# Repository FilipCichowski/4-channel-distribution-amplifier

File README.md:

# 4-channel-distribution-amplifier

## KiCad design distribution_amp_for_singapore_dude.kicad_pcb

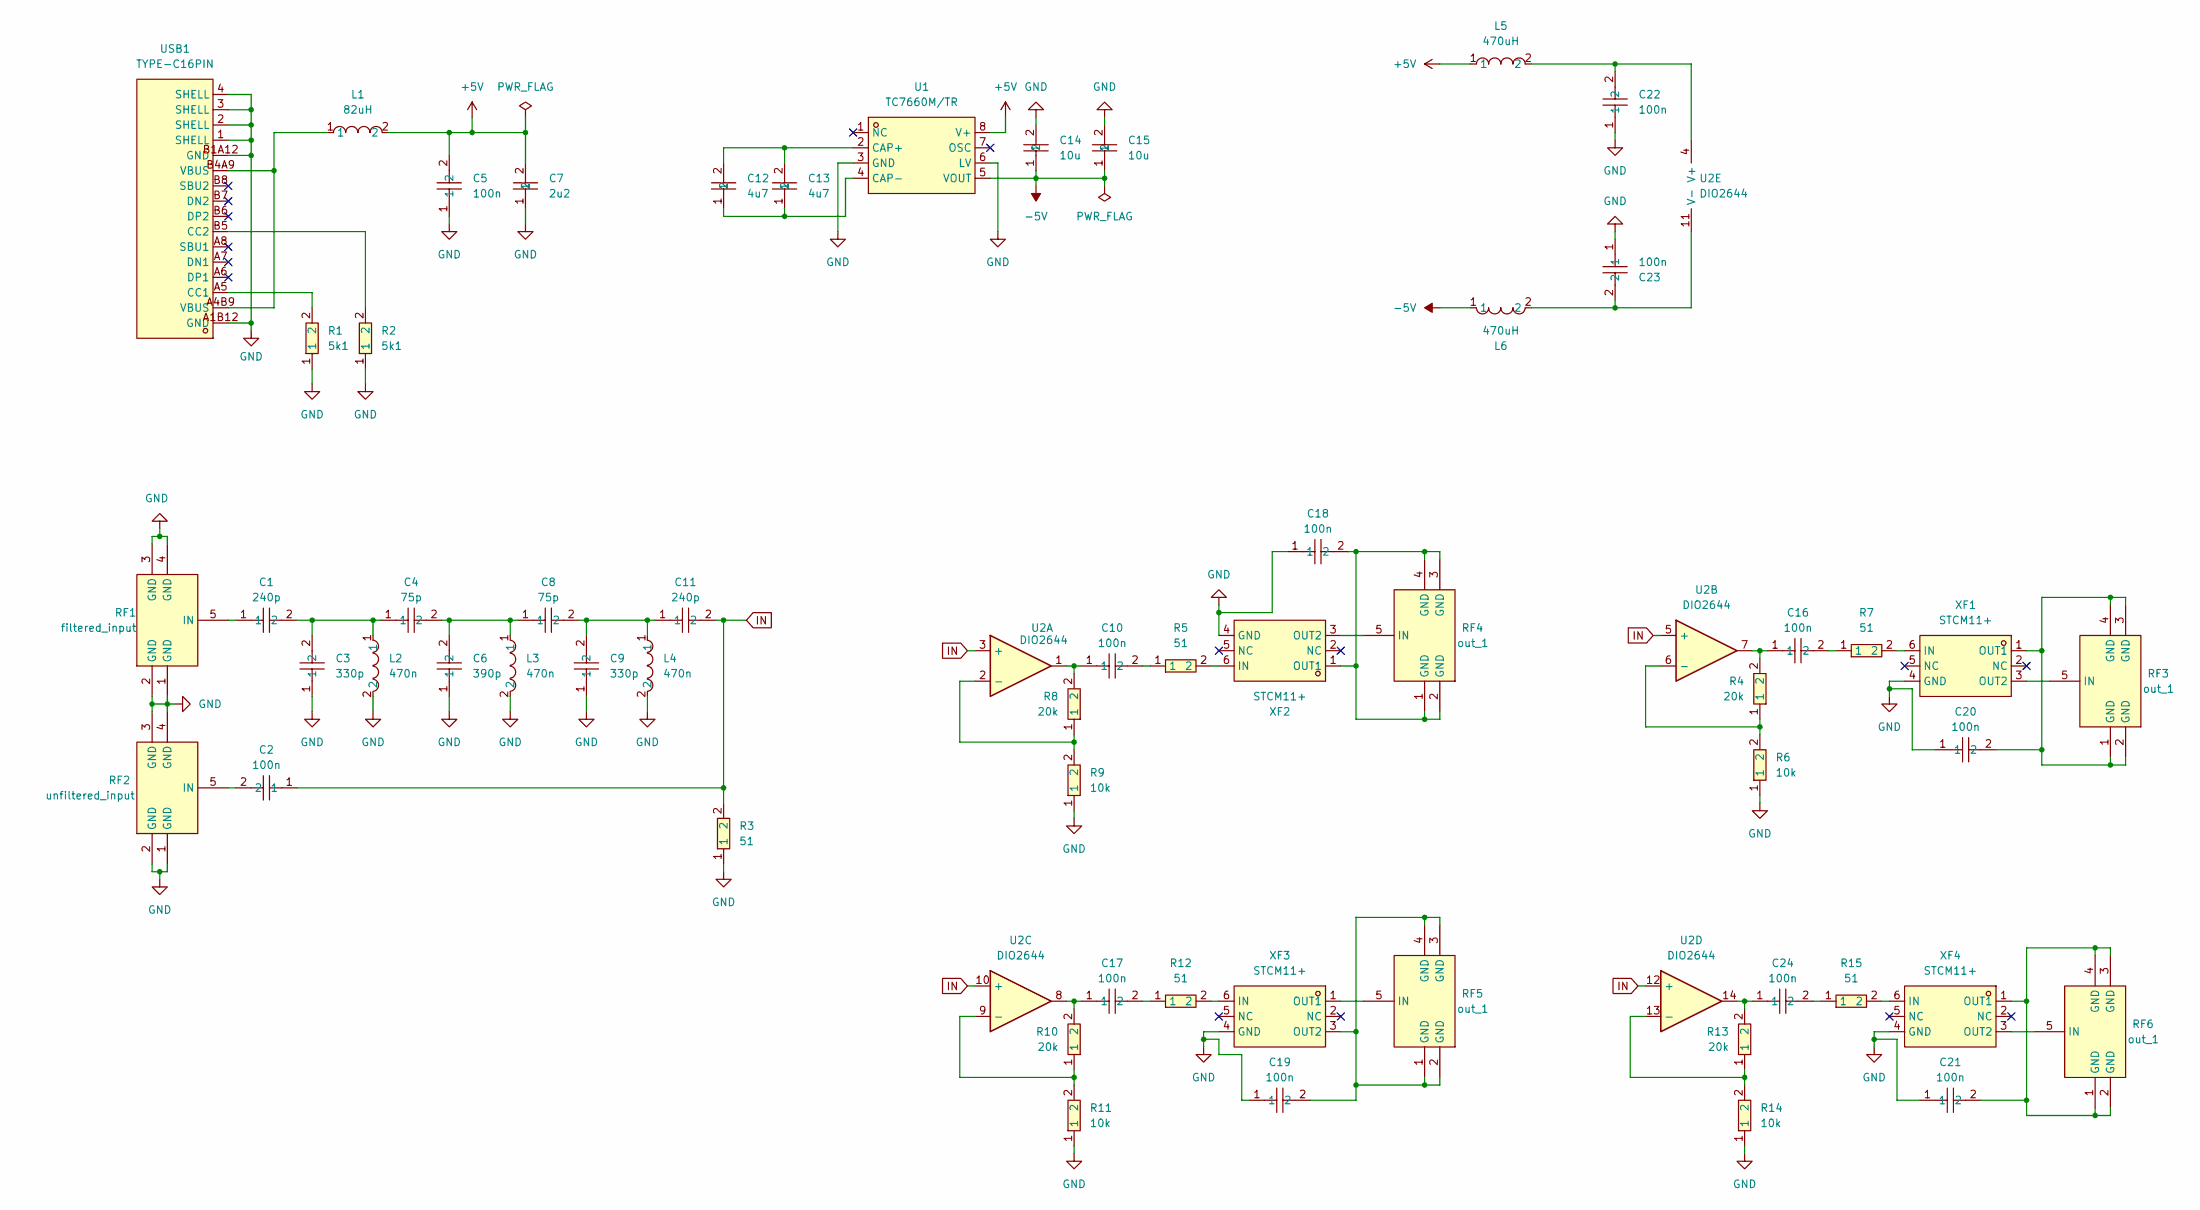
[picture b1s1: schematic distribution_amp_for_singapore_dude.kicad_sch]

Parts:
C1, C11: 240p; C0805; LCSC Part C520005
C2, C5, C10, C16, C17, C18, C19, C20, C21, C22, C23, C24: 100n; C0805; LCSC Part C49678
C3, C9: 330p; C0805; LCSC Part C282701
C4, C8: 75p; C0805; LCSC Part C541521
C6: 390p; C0805; LCSC Part C527206
C7: 2u2; C1206; LCSC Part C50254
C12, C13: 4u7; C1206; LCSC Part C29823
C14, C15: 10u; C1206; LCSC Part C13585
L1: 82uH; IND-SMD_L4.5-W4.0_CD43; LCSC Part C2880035
L2, L3, L4: 470n; L0805; LCSC Part C139228
L5, L6: 470uH; IND-SMD_L4.0-W4.0; LCSC Part C2827387
R1, R2: 5k1; R0805; LCSC Part C27834
R3, R5, R7, R12, R15: 51; R0805; LCSC Part C27834
R4, R8, R10, R13: 20k; R0805; LCSC Part C4328
R6, R9, R11, R14: 10k; R0805; LCSC Part C17414
RF1: filtered_input; ANT-TH_KH-SMA-K513-G; LCSC Part C411575
RF2: unfiltered_input; ANT-TH_KH-SMA-K513-G; LCSC Part C411575
RF3, RF4, RF5, RF6: out_1; ANT-TH_KH-SMA-K513-G; LCSC Part C411575
U1: TC7660M/TR; SOP-8_L4.9-W3.9-P1.27-LS6.0-BL; LCSC Part C512761
U2: DIO2644; TSSOP-14_4.4x5mm_P0.65mm
USB1: TYPE-C16PIN; USB-C-SMD_TYPE-C16PIN; LCSC Part C393939
XF1, XF2, XF3, XF4: STCM11+; XFMR-SMD_STCM11; LCSC Part C5178925

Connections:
+5V: C5.2, C7.2, L1.2, L5.1, U1.8 (V+)
-5V: C14.1, C15.1, L6.1, U1.5 (VOUT)
GND: C3.1, C5.1, C6.1, C7.1, C9.1, C14.2, C15.2, C18.1, C19.1, C20.1, C21.1, C22.1, C23.1, L2.2, L3.2, L4.2, R1.1, R2.1, R3.1, R6.1, R9.1, R11.1, R14.1, RF1.1 (GND), RF1.2 (GND), RF1.3 (GND), RF1.4 (GND), RF2.1 (GND), RF2.2 (GND), RF2.3 (GND), RF2.4 (GND), U1.3 (GND), U1.6 (LV), USB1.1 (SHELL), USB1.2 (SHELL), USB1.3 (SHELL), USB1.4 (SHELL), USB1.A1B12 (GND), USB1.B1A12 (GND), XF1.4 (GND), XF2.4 (GND), XF3.4 (GND), XF4.4 (GND)
IN: C2.1, C11.2, R3.2, U2.3 (+), U2.5 (+), U2.10 (+), U2.12 (+)
unnamed: C1.2, C3.2, C4.1, L2.1
unnamed: C4.2, C6.2, C8.1, L3.1
unnamed: C10.1, R8.2, U2.1
unnamed: C10.2, R5.1
unnamed: C8.2, C9.2, C11.1, L4.1
unnamed: C16.1, R4.2, U2.7
unnamed: C16.2, R7.1
unnamed: C17.1, R10.2, U2.8
unnamed: C17.2, R12.1
unnamed: C24.1, R13.2, U2.14
unnamed: C24.2, R15.1
unnamed: L1.1, USB1.A4B9 (VBUS), USB1.B4A9 (VBUS)
unnamed: C1.1, RF1.5 (IN)
unnamed: C2.2, RF2.5 (IN)
unnamed: RF3.5 (IN), XF1.3 (OUT2)
unnamed: RF4.5 (IN), XF2.3 (OUT2)
unnamed: RF5.5 (IN), XF3.1 (OUT1)
unnamed: RF6.5 (IN), XF4.3 (OUT2)
unnamed: C12.2, C13.2, U1.2 (CAP+)
unnamed: C12.1, C13.1, U1.4 (CAP-)
unnamed: R8.1, R9.2, U2.2 (-)
unnamed: R4.1, R6.2, U2.6 (-)
unnamed: R10.1, R11.2, U2.9 (-)
unnamed: R13.1, R14.2, U2.13 (-)
unnamed: C22.2, L5.2, U2.4 (V+)
unnamed: C23.2, L6.2, U2.11 (V-)
unnamed: R1.2, USB1.A5 (CC1)
unnamed: R2.2, USB1.B5 (CC2)
unnamed: R7.2, XF1.6 (IN)
unnamed: C20.2, RF3.1 (GND), RF3.2 (GND), RF3.3 (GND), RF3.4 (GND), XF1.1 (OUT1)
unnamed: R5.2, XF2.6 (IN)
unnamed: C18.2, RF4.1 (GND), RF4.2 (GND), RF4.3 (GND), RF4.4 (GND), XF2.1 (OUT1)
unnamed: R12.2, XF3.6 (IN)
unnamed: C19.2, RF5.1 (GND), RF5.2 (GND), RF5.3 (GND), RF5.4 (GND), XF3.3 (OUT2)
unnamed: R15.2, XF4.6 (IN)
unnamed: C21.2, RF6.1 (GND), RF6.2 (GND), RF6.3 (GND), RF6.4 (GND), XF4.1 (OUT1)

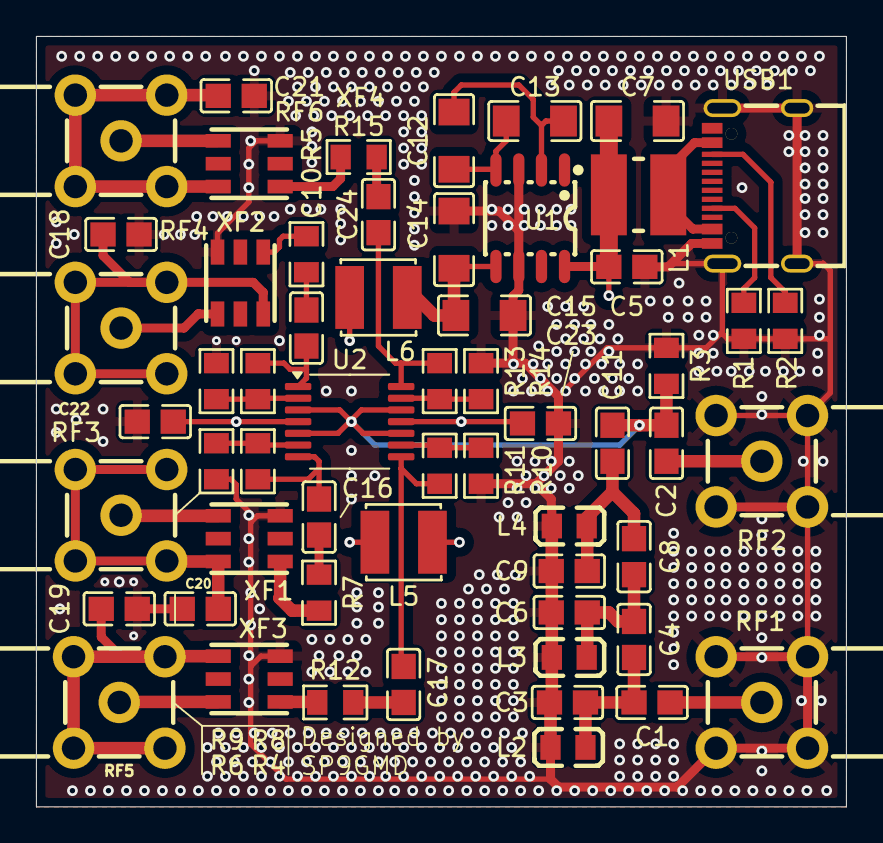
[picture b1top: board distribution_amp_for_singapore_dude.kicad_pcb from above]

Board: 4 copper layers, 45.0 x 42.8 mm, 58 parts (0 on the bottom side), 40 nets.

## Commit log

2025-08-14 Added project files
